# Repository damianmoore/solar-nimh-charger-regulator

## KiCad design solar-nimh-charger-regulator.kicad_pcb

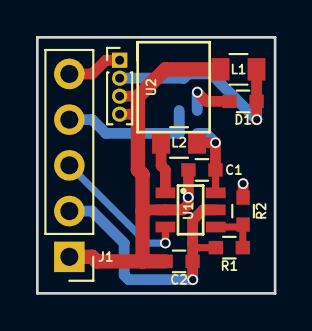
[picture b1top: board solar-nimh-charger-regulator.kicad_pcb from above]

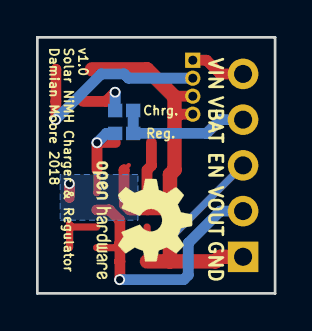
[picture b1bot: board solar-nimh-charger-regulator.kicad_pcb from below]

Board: 2 copper layers, 13.2 x 14.2 mm, 12 parts (2 on the bottom side), 10 nets.

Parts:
C1, C2: C; C_0603
Chrg.: SW_SPST; Solder_Bridge
D1: D_Schottky; C_0603
J1: Conn_01x05; Pin_Header_Straight_1x05_Pitch2.54mm
L1, L2: L; C_0805
R1, R2: R; C_0603
Reg.: SW_SPST; Solder_Bridge
U1: TPS61070; SOT-23-6
U2: YX805; YX805-Angled

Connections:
EN: J1.3, U1.3
GND: C1.2, C2.2, J1.1, L1.2, R2.2, U1.2, U2.3, U2.4
unnamed: C1.1, L2.1, Reg..2, U1.6
unnamed: Chrg..1, D1.1
unnamed: D1.2, L1.1, U2.2
unnamed: L2.2, U1.1
unnamed: R1.2, R2.1, U1.4
VBAT: Chrg..2, J1.4, Reg..1
VIN: J1.5, U2.1
VOUT: C2.1, J1.2, R1.1, U1.5

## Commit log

2018-05-29 Solar NiMH charger and regulator v1.0
2018-06-14 Added values to passive components
2018-07-07 Voltage divider values
